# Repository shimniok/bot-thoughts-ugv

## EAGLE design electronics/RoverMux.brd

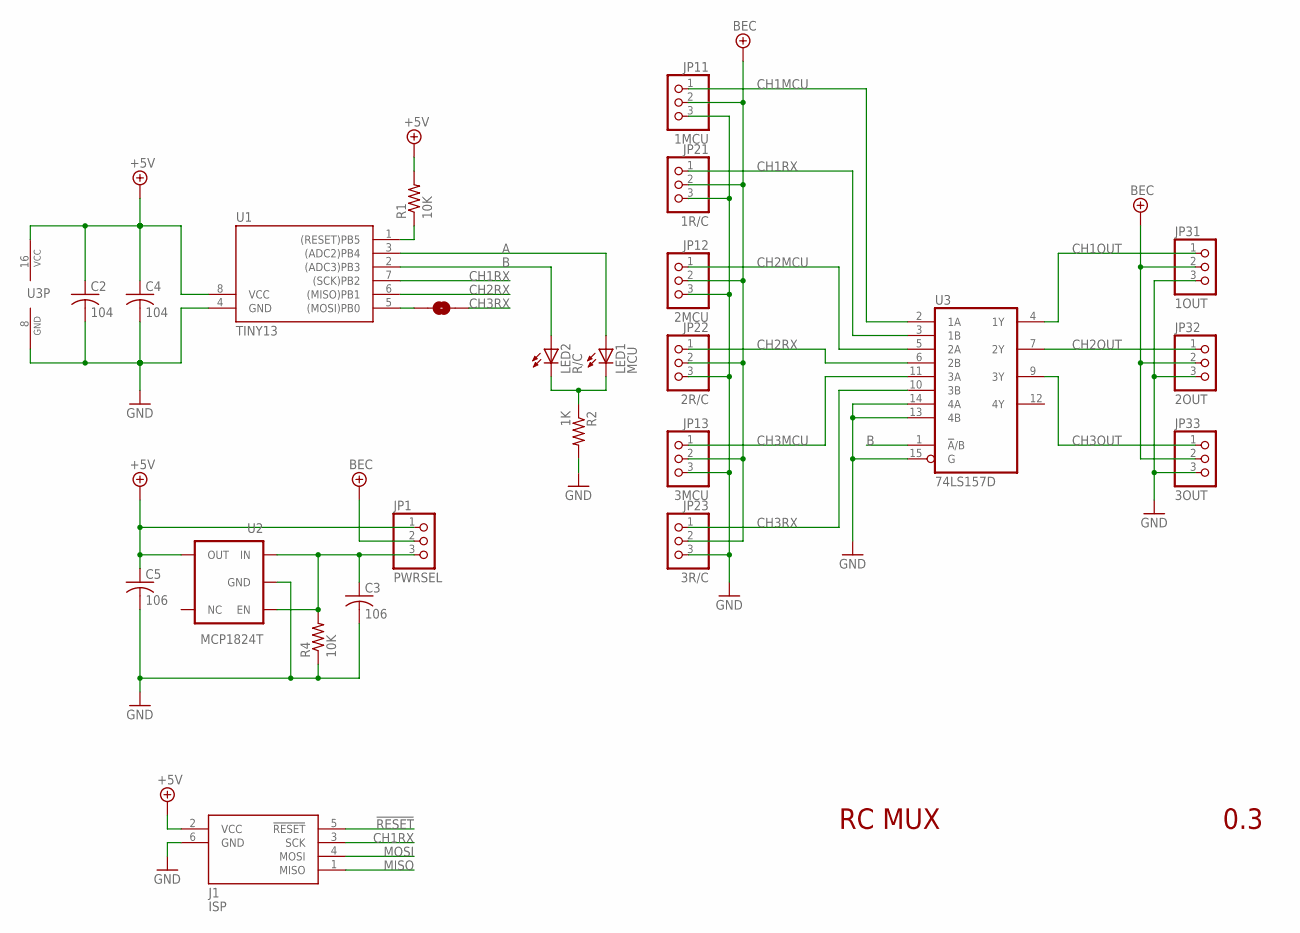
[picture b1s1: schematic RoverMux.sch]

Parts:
C2, C4: 104; C0603; PARTNO C1608X7R1E104K080AA
C3, C5: 106; C0603; PARTNO CL10A106MP8NNNC
J1: ISP; CON6P2R
JP1: PWRSEL; 1X03M
JP11: 1MCU; 1X03-S
JP12: 2MCU; 1X03-S
JP13: 3MCU; 1X03-S
JP21: 1R/C; 1X03-S
JP22: 2R/C; 1X03-S
JP23: 3R/C; 1X03-S
JP31: 1OUT; 1X03-S
JP32: 2OUT; 1X03-S
JP33: 3OUT; 1X03-S
LED1: MCU; CHIPLED_1206; PARTNO LH N974-KN-1
LED2: R/C; CHIPLED_1206; PARTNO LG N971-KN-1
R1, R4: 10K; R0603; PARTNO 1622829-1
R2: 1K; R0603; PARTNO RC0603JR-07330RL
SJ1: CH3; SJ_2S-NOTRACE
U1: TINY13; SO08; PARTNO ATTINY13A-SSH
U2: MCP1824T; SOT23-5; PARTNO MCP1824T-5002E/OT
U3: 74LS157D; SO16; PARTNO 74HCT157D,652

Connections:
!RESET: J1.5 (!RESET), R1.1, U1.1 ((RESET)PB5)
+5V: C2.1, C4.1, C5.1, J1.2 (VCC), JP1.1, R1.2, U1.8 (VCC), U2.5 (OUT), U3.16 (VCC)
+7V: JP1.2, JP11.2, JP12.2, JP13.2, JP21.2, JP22.2, JP23.2, JP31.2, JP32.2, JP33.2
A: LED1.A, U1.3 ((ADC2)PB4)
B: LED2.A, U1.2 ((ADC3)PB3), U3.1 (!A!/B)
CH1MCU: JP11.1, U3.2 (1A)
CH1OUT: JP31.1, U3.4 (1Y)
CH1RX: J1.3 (SCK), JP21.1, U1.7 ((SCK)PB2), U3.3 (1B)
CH2MCU: JP12.1, U3.5 (2A)
CH2OUT: JP32.1, U3.7 (2Y)
CH2RX: JP22.1, U1.6 ((MISO)PB1), U3.6 (2B)
CH3MCU: JP13.1, U3.11 (3A)
CH3OUT: JP33.1, U3.9 (3Y)
CH3RX: JP23.1, SJ1.2, U3.10 (3B)
GND: C2.2, C3.2, C4.2, C5.2, J1.6 (GND), JP11.3, JP12.3, JP13.3, JP21.3, JP22.3, JP23.3, JP31.3, JP32.3, JP33.3, R2.2, R4.1, U1.4 (GND), U2.2 (GND), U3.8 (GND), U3.13 (4B), U3.14 (4A), U3.15 (G)
MISO: J1.1 (MISO)
MOSI: J1.4 (MOSI), SJ1.1, U1.5 ((MOSI)PB0)
unnamed: LED1.C, LED2.C, R2.1
REGIN: C3.1, JP1.3, R4.2, U2.1 (IN), U2.3 (EN)

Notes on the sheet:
RC MUX
0.3

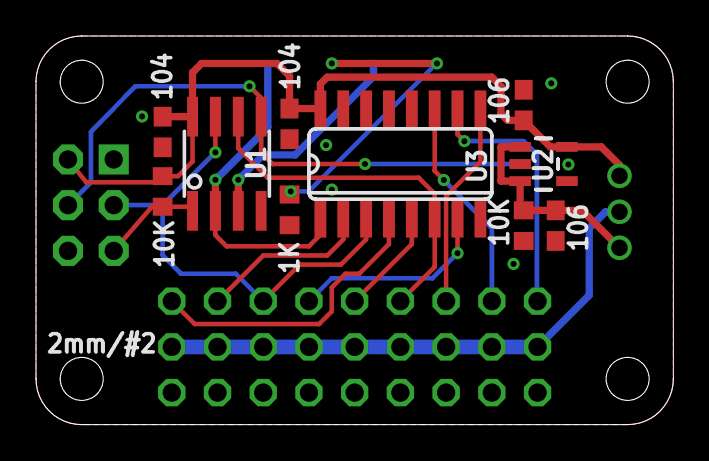
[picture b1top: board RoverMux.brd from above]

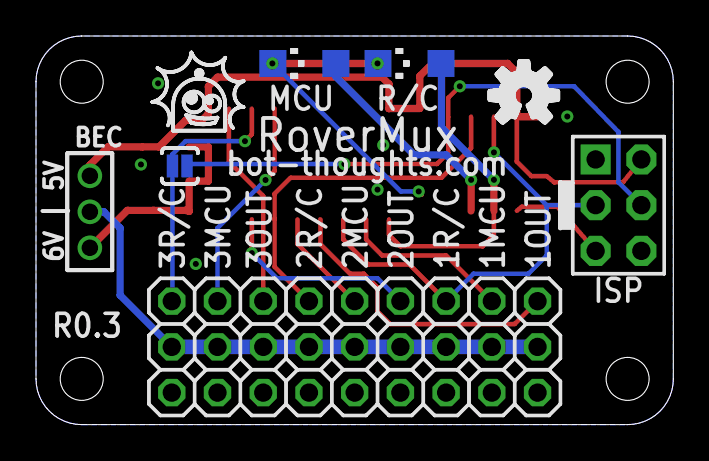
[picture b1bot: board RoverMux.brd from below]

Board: 2 copper layers, 35.4 x 21.6 mm, 24 parts (14 on the bottom side), 18 nets.

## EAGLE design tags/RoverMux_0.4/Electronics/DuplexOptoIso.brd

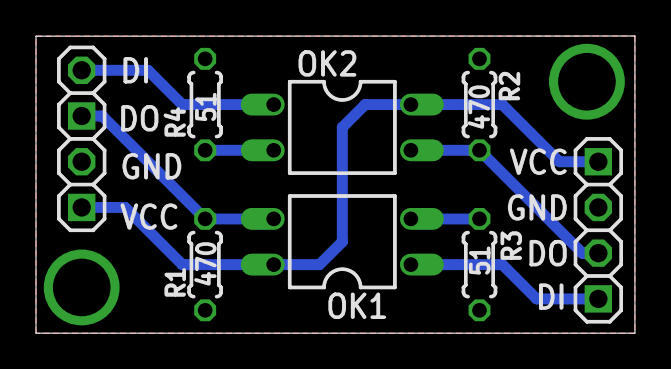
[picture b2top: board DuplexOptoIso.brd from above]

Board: 2 copper layers, 33.3 x 16.5 mm, 10 parts (0 on the bottom side), 8 nets.

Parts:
JP1: 1IN2OUT; 1X02-S
JP2: 1OUT2IN; 1X02-S
JP3, JP4: POWER; 1X02-S
OK1, OK2: PC817; DIL04
R1, R2: 470; 0204/5
R3, R4: 51; 0204/5

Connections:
5V: JP3.1, JP4.1, OK1.4, OK2.4
GND: JP3.2, JP4.2, R1.1, R2.1, R3.1, R4.1
IN1: JP1.1, OK1.1
IN2: JP2.2, OK2.1
unnamed: OK1.2, R3.2
unnamed: OK2.2, R4.2
OUT1: JP2.1, OK1.3, R1.2
OUT2: JP1.2, OK2.3, R2.2

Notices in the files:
parts and their libraries:
SparkFun: Licensing: CC v3.0 Share-Alike You are welcome to use this library for commercial purposes.
